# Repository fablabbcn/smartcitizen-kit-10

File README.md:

Smart Citizen Kit
=================

**NOTE:** [Click here](https://github.com/fablabbcn/smartcitizen-kit-20) for the newer version of SCK 2.0+

**Smart Citizen Kit BETA version for the Ambient Sensor Board.**

### Download

* Download the latest firmware release [here](https://github.com/fablabbcn/Smart-Citizen-Kit/releases/latest).

### Hardware

* Firmware for the [SmartCitizen Ambient Kit](http://smartcitizen.me/pages/sck) 1.0 and 1.1.

* More hardware info [here](https://github.com/fablabbcn/Smart-Citizen-Kit/tree/master/hardware).

### Quick start

* Visit the project main documentation [docs.smartcitizen.me](http://docs.smartcitizen.me)

### Loading Firmware

**The firmware is totally compatible with Arduino. You can upload the firmware using the [Arduino IDE](http://arduino.cc/en/main/software).**

* For SmartCitizen Kit version 1.0 select `Tools/Boards/Arduino Leonardo` on the Arduino IDE (ATmega 32U4 at 16Mhz) 

* For SmartCitizen Kit version 1.1 select `Tools/Boards/Lylipad Arduino USB` on the Arduino IDE (ATmega 32U4 at 8Mhz) 

### Versions

The current firmware version in use is `0.9.4`.

We currently support the SD card version on as a diferent firmware `SDCARD`, currently `0.8.7 SDCARD`.

You can see the release history [here](https://github.com/fablabbcn/Smart-Citizen-Kit/releases)

You can see the hardware versions [here](https://github.com/fablabbcn/Smart-Citizen-Kit/blob/master/hardware/README.md)

### Advance References

* Setup commands reference in [sck-commands.md](https://github.com/fablabbcn/Smart-Citizen-Kit/blob/master/sck-commands.md)

* Basic documentation for creating your own Sensor Boards [here](https://github.com/fablabbcn/Smart-Citizen-Kit/wiki/Making-a-Shield)

* [Slideshow](https://speakerdeck.com/pral2a/smart-citizen-hardware-and-software) with project technical details

### Support and issues

* Forum [forum.smartcitizen.me](http://forum.smartcitizen.me)

### Contributions

* We are working on improving the firmware documentation for developers but still we encourage you to Fork the project and do a Pull request with your contributions.

## License

All the software unless stated is released under [GNU GPL v3.0](https://github.com/fablabbcn/smartcitizen-kit/blob/master/LICENSE) and the hardware design files under [CERN OHL v1.2](https://github.com/fablabbcn/smartcitizen-kit/blob/master/hardware/LICENSE)

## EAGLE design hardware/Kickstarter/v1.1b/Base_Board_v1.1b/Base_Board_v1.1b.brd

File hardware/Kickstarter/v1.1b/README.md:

Smart-Citizen-Kit
=================

Eagles files of the Kickstarter campaign

[https://www.kickstarter.com/projects/acrobotic/the-smart-citizen-kit-crowdsourced-environmental-m
](https://www.kickstarter.com/projects/acrobotic/the-smart-citizen-kit-crowdsourced-environmental-m)

Smart Citizen Kit BETA version
- Base Board v1.1b
- Ambient Sensor Board v1.1b

The SCK is a piece of hardware comprised by two printed-circuit boards: an interchangeable daughterboard or shield, and an arduino-compatible data-processing board.

The sensor board carries sensors that measure air composition (CO and NO2), temperature, light intensity, sound levels, and humidity. Once it's set up, the ambient board is able to stream data measured by the sensors over Wi-Fi using the FCC-certified, wireless module on the data-processing board.

LICENSE: GPL v.0.3

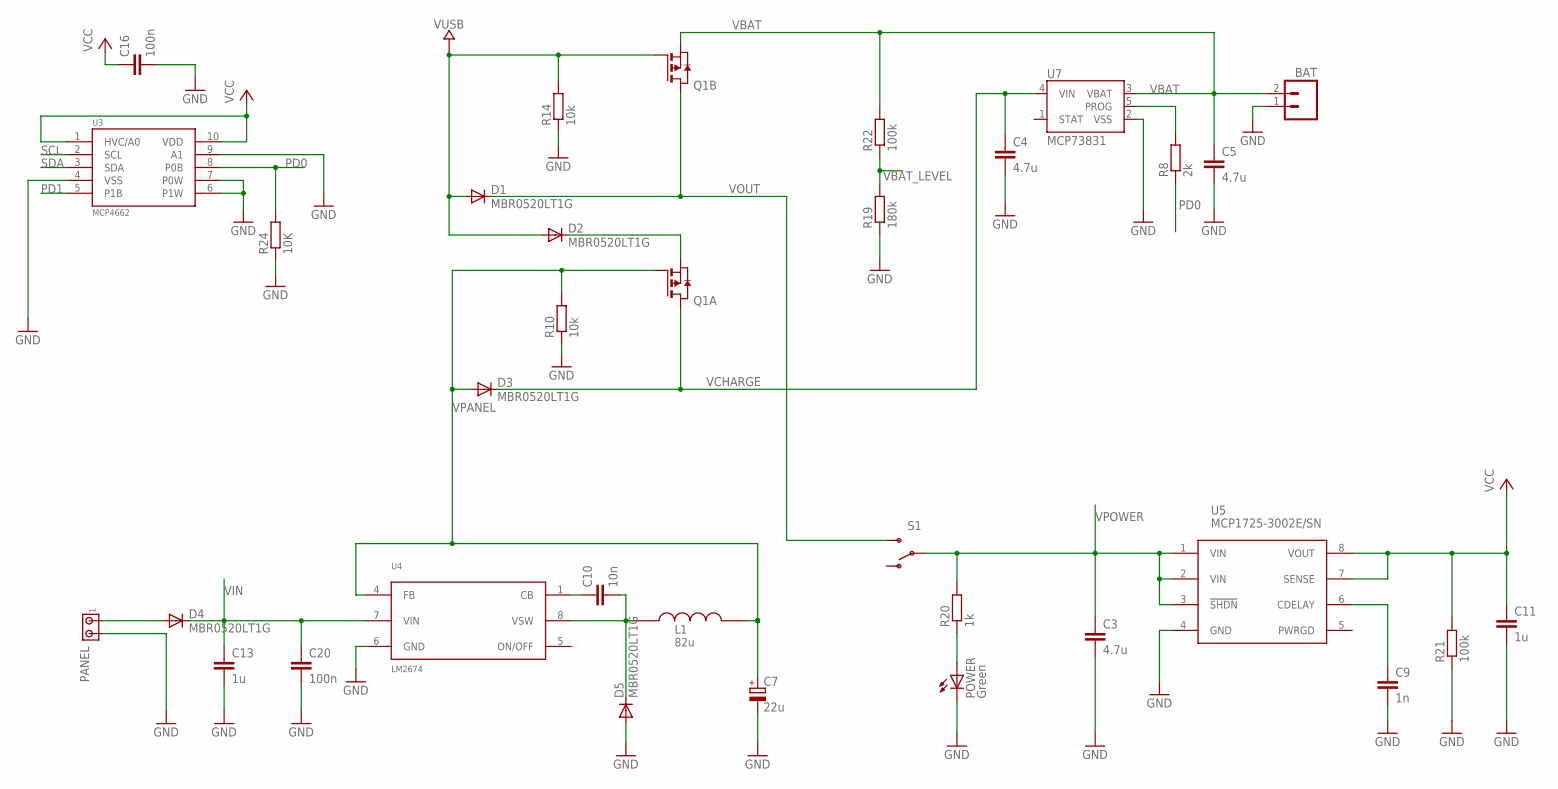
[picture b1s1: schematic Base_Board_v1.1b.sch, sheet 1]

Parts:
BAT: M02-JST-2MM-SMT; S2B-PH
C3, C4, C5: 4.7u; C0805
C7: 22u; SMC_A
C9: 1n; C0603K
C10: 10n; C0603K
C11, C13: 1u; C0805
C16, C20: 100n; C0603K
D1, D2, D3, D4, D5: MBR0520LT1G; SOD123
L1: 82u; SDR1006
PANEL: MTA02-100; 10X02MTA
POWER: Green; CHIP-LED0805
Q1: PMOS2SO8; SO8
R8: 2k; R0603
R10, R14: 10k; R0603
R19: 180k; R0603
R20: 1k; R0603
R21, R22: 100k; R0603
R24: 10K; R0603
S1: SWITCH-SPST-SMD-A
U3: MCP4662; MSOP10
U4: LM2674; SO8
U5: MCP1725-3002E/SN; SOIC8
U7: MCP73831; SOT23-5

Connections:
GND: BAT.1, C3.2, C4.2, C5.2, C7.-, C9.2, C11.2, C13.2, C16.2, C20.2, D5.A, PANEL.2, POWER.C, R10.1, R14.1, R19.1, R21.1, R24.1, U3.4 (VSS), U3.6 (P1W), U3.7 (P0W), U3.9 (A1), U4.6 (GND), U5.4 (GND), U7.2 (VSS); also elsewhere on the board
unnamed: D2.C, Q1.1 (S)
unnamed: D4.A, PANEL.1
unnamed: C9.1, U5.6 (CDELAY)
unnamed: R8.2, U7.5 (PROG)
unnamed: POWER.A, R20.1
unnamed: C10.1, U4.1 (CB)
unnamed: C10.2, D5.C, L1.1, U4.8 (VSW)
PD0: R8.1, R24.2, U3.8 (P0B)
PD1: U3.5 (P1B)
SCL: U3.2 (SCL); also elsewhere on the board
SDA: U3.3 (SDA); also elsewhere on the board
VBAT: BAT.2, C5.1, Q1.3 (S), R22.2, U7.3 (VBAT)
VBAT_LEVEL: R19.2, R22.1; also elsewhere on the board
VCC: C11.1, C16.1, R21.2, U3.1 (HVC/A0), U3.10 (VDD), U5.7 (SENSE), U5.8 (VOUT); also elsewhere on the board
VCHARGE: C4.1, D3.C, Q1.7 (D), Q1.8 (D), U7.4 (VIN)
VIN: C13.1, C20.1, D4.C, U4.7 (VIN); also elsewhere on the board
VOUT: D1.C, Q1.5 (D), Q1.6 (D), S1.3 (S)
VPANEL: C7.+, D3.A, L1.2, Q1.2 (G), R10.2, U4.4 (FB)
VPOWER: C3.1, R20.2, S1.2, U5.1 (VIN), U5.2 (VIN), U5.3 (!SHDN); also elsewhere on the board
VUSB: D1.A, D2.A, Q1.4 (G), R14.2; also elsewhere on the board

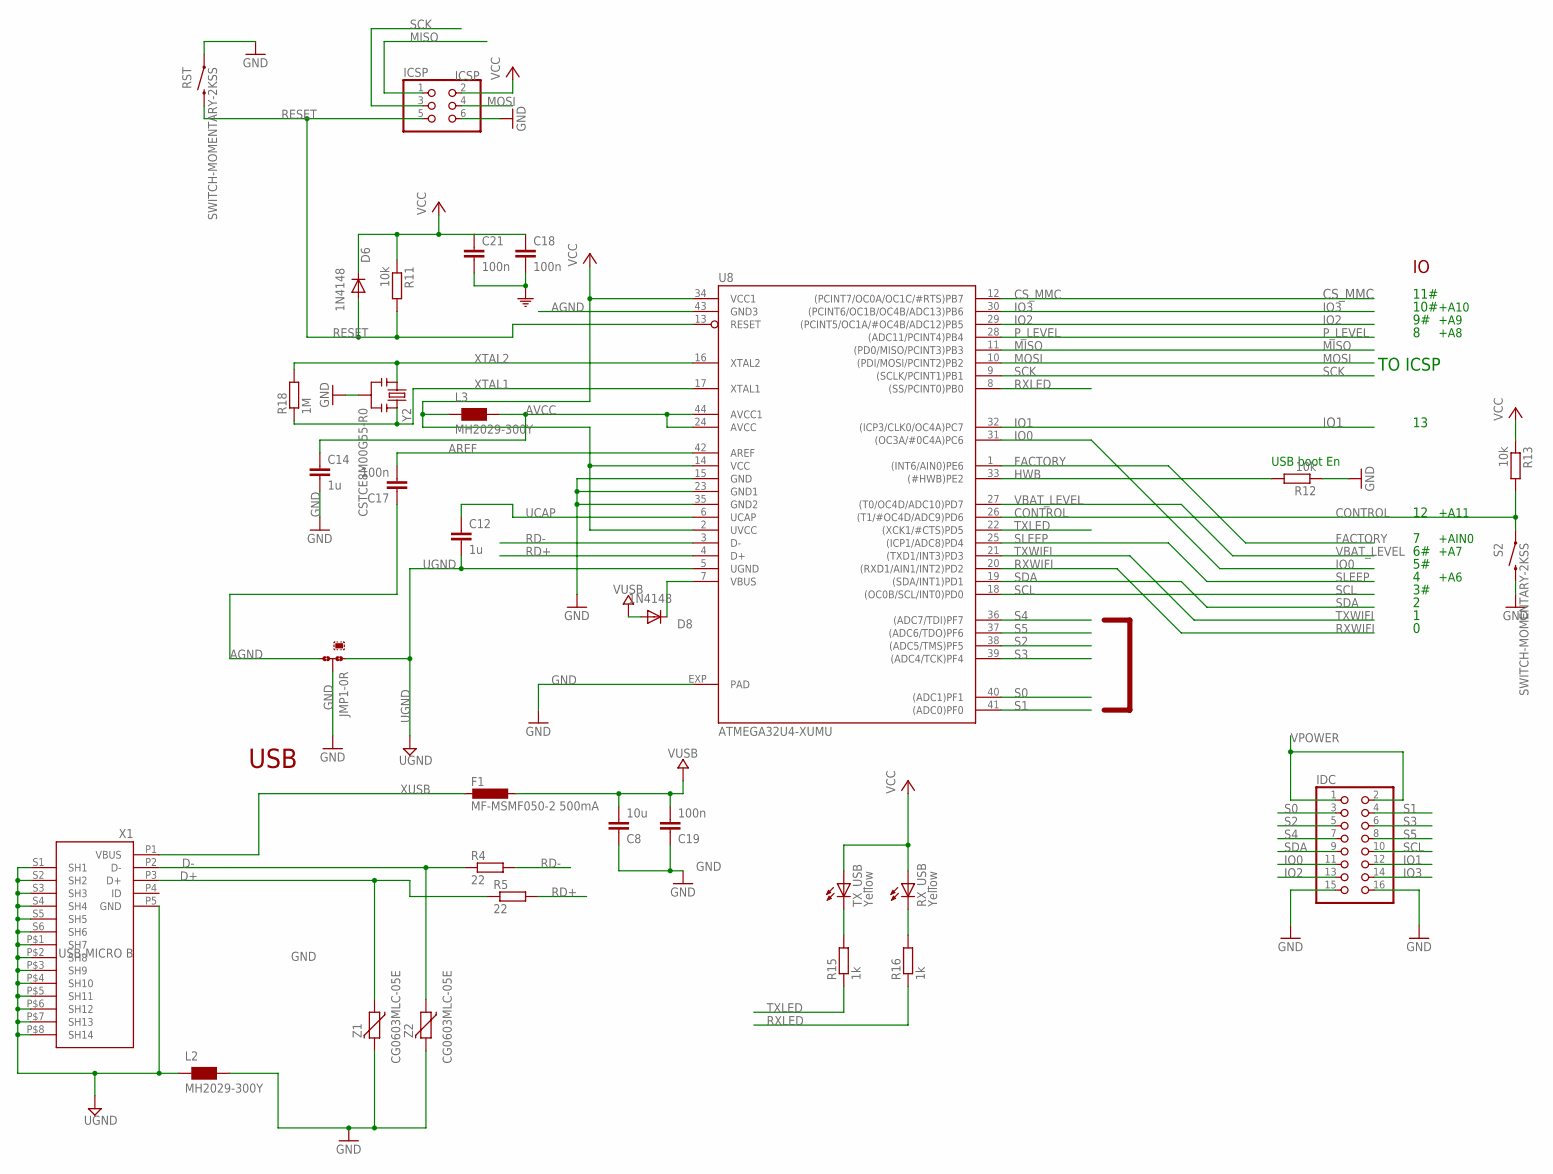
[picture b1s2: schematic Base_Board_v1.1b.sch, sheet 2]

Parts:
C8: 10u; C0805
C12, C14: 1u; C0805
C17, C18, C19, C21: 100n; C0603K
D6, D8: 1N4148; SOD323-W
F1: MF-MSMF050-2 500mA; L1812
ICSP: ICSP; 2X03
IDC: PINHD-2X8; 2X08
JMP1: 0R-JUMPC; C0R-JMP
L2, L3: MH2029-300Y; 0805
R4, R5: 22; R0603
R11, R12, R13: 10k; R0603
R15, R16: 1k; R0603
R18: 1M; R0603
RST: SWITCH-MOMENTARY-2KSS; KSS241G
RX_USB: Yellow; CHIP-LED0805
S2: SWITCH-MOMENTARY-2KSS; KSS241G
TX_USB: Yellow; CHIP-LED0805
U8: ATMEGA32U4-XUMU; QFN44ML7X7
X1: USB-MICRO B; CON2_USB_MICRO_B_AT
Y2: CSTCE8M00G55-R0
Z1, Z2: CG0603MLC-05E; CT/CN0603

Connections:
AGND: C17.1, JMP1.3, U8.43 (GND3)
AREF: C17.2, U8.42 (AREF)
AVCC: C14.1, L3.2, U8.24 (AVCC), U8.44 (AVCC1)
CONTROL: R13.2, S2.1, U8.26 ((T1/#OC4D/ADC9)PD6)
CS_MMC: U8.12 ((PCINT7/OC0A/OC1C/#RTS)PB7); also elsewhere on the board
D+: R5.1, X1.P3 (D+), Z1.1
D-: R4.1, X1.P2 (D-), Z2.1
FACTORY: U8.1 ((INT6/AIN0)PE6); also elsewhere on the board
GND: C8.1, C14.2, C18.2, C19.1, C21.2, ICSP.6, IDC.15, IDC.16, JMP1.2, L2.2, R12.1, RST.1, S2.2, U8.15 (GND), U8.23 (GND1), U8.35 (GND2), U8.EXP (PAD), Y2.2, Z1.2, Z2.2; also elsewhere on the board
GND1: L2.1, X1.P5 (GND), X1.P$1 (SH7), X1.P$2 (SH8), X1.P$3 (SH9), X1.P$4 (SH10), X1.P$5 (SH11), X1.P$6 (SH12), X1.P$7 (SH13), X1.P$8 (SH14), X1.S1 (SH1), X1.S2 (SH2), X1.S3 (SH3), X1.S4 (SH4), X1.S5 (SH5), X1.S6 (SH6)
HWB: R12.2, U8.33 ((#HWB)PE2)
IO0: IDC.11, U8.31 ((OC3A/#0C4A)PC6)
IO1: IDC.12, U8.32 ((ICP3/CLK0/OC4A)PC7)
IO2: IDC.13, U8.29 ((PCINT5/OC1A/#OC4B/ADC12)PB5)
IO3: IDC.14, U8.30 ((PCINT6/OC1B/OC4B/ADC13)PB6)
MISO: ICSP.1, U8.11 ((PD0/MISO/PCINT3)PB3); also elsewhere on the board
MOSI: ICSP.4, U8.10 ((PDI/MOSI/PCINT2)PB2); also elsewhere on the board
unnamed: R15.2, TX_USB.C
unnamed: R16.2, RX_USB.C
unnamed: D8.C, U8.7 (VBUS)
P_LEVEL: U8.28 ((ADC11/PCINT4)PB4); also elsewhere on the board
RD+: R5.2, U8.4 (D+)
RD-: R4.2, U8.3 (D-)
RESET: D6.A, ICSP.5, R11.2, RST.2, U8.13 (RESET); also elsewhere on the board
RXLED: R16.1, U8.8 ((SS/PCINT0)PB0)
RXWIFI: U8.20 ((RXD1/AIN1/INT2)PD2); also elsewhere on the board
S0: IDC.3, U8.40 ((ADC1)PF1)
S1: IDC.4, U8.41 ((ADC0)PF0)
S2: IDC.5, U8.38 ((ADC5/TMS)PF5)
S3: IDC.6, U8.39 ((ADC4/TCK)PF4)
S4: IDC.7, U8.36 ((ADC7/TDI)PF7)
S5: IDC.8, U8.37 ((ADC6/TDO)PF6)
SCK: ICSP.3, U8.9 ((SCLK/PCINT1)PB1); also elsewhere on the board
SCL: IDC.10, U8.18 ((OC0B/SCL/INT0)PD0); also elsewhere on the board
SDA: IDC.9, U8.19 ((SDA/INT1)PD1); also elsewhere on the board
SLEEP: U8.25 ((ICP1/ADC8)PD4); also elsewhere on the board
TXLED: R15.1, U8.22 ((XCK1/#CTS)PD5)
TXWIFI: U8.21 ((TXD1/INT3)PD3); also elsewhere on the board
UCAP: C12.1, U8.6 (UCAP)
UGND: C12.2, JMP1.1, U8.5 (UGND)
VBAT_LEVEL: U8.27 ((T0/OC4D/ADC10)PD7); also elsewhere on the board
VCC: C18.1, C21.1, D6.C, ICSP.2, L3.1, R11.1, R13.1, RX_USB.A, TX_USB.A, U8.2 (UVCC), U8.14 (VCC), U8.34 (VCC1); also elsewhere on the board
VPOWER: IDC.1, IDC.2; also elsewhere on the board
VUSB: C8.2, C19.2, D8.A, F1.1; also elsewhere on the board
XTAL1: R18.1, U8.17 (XTAL1), Y2.3
XTAL2: R18.2, U8.16 (XTAL2), Y2.1
XUSB: F1.2, X1.P1 (VBUS)

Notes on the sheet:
USB boot En
USB
TO ICSP
10#
11#
+A6
+A11
+A10
+A9
+A7
+A8
+AIN0

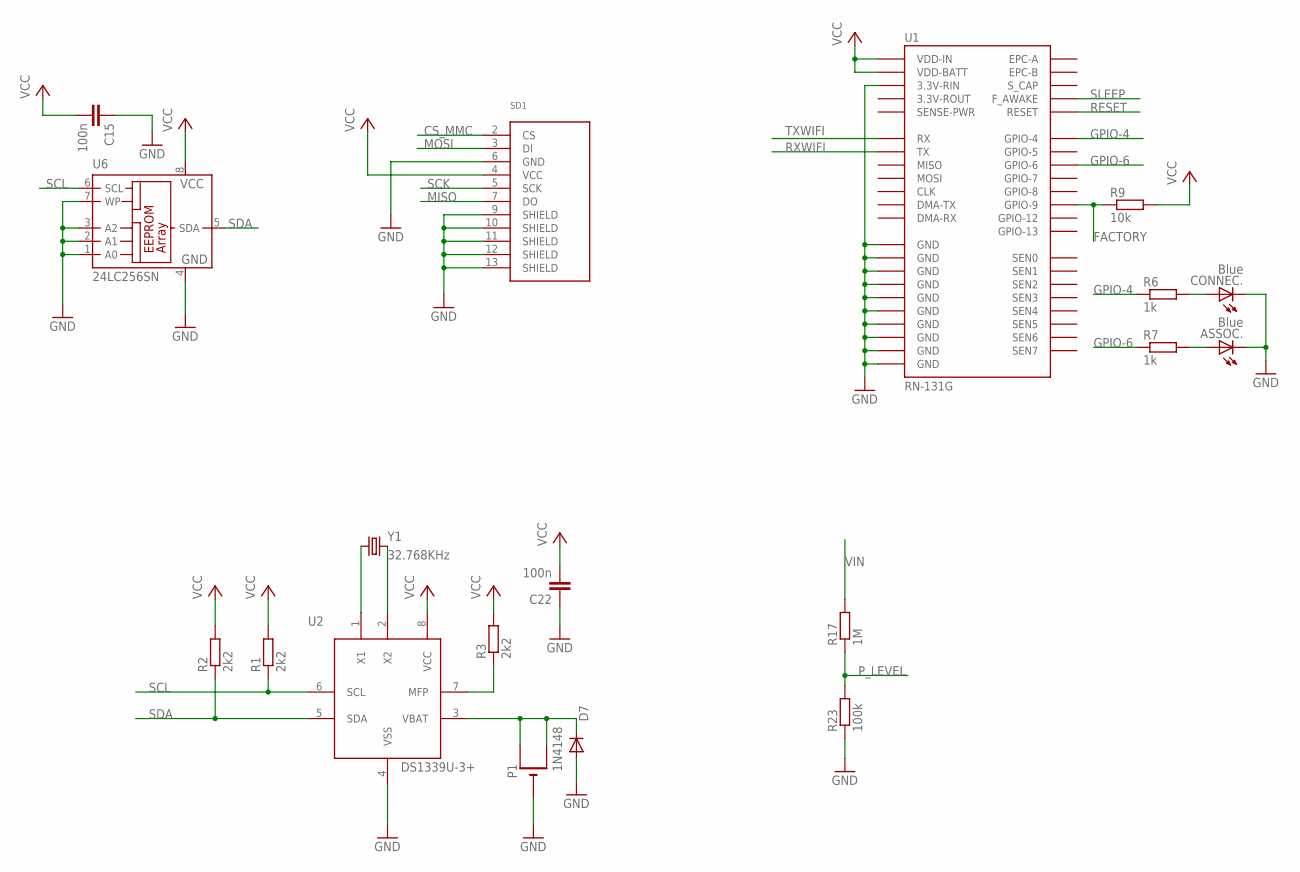
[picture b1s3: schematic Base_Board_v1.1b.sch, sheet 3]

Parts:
ASSOC.: Blue; CHIP-LED0805
C15, C22: 100n; C0603K
CONNEC.: Blue; CHIP-LED0805
D7: 1N4148; SOD323-W
P1: CR1220SMT; CR1220-SMD
R1, R2, R3: 2k2; R0603
R6, R7: 1k; R0603
R9: 10k; R0603
R17: 1M; R0603
R23: 100k; R0603
SD1: SD_CARD_SOCKETDM3CS; DM3CS
U1: RN-131G
U2: DS1339U-3+; MSOP-8
U6: 24LC256SN; SO-08
Y1: 32.768KHz; ABS10

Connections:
CS_MMC: SD1.2 (CS); also elsewhere on the board
FACTORY: R9.1, U1.P$24 (GPIO-9); also elsewhere on the board
GND: ASSOC..C, C15.1, C22.1, CONNEC..C, D7.A, P1.-, R23.1, SD1.6 (GND), SD1.9 (SHIELD), SD1.10 (SHIELD), SD1.11 (SHIELD), SD1.12 (SHIELD), SD1.13 (SHIELD), U1.P$18 (3.3V-RIN), U1.P$19 (GND), U1.P$36 (GND), U1.P$37 (GND), U1.P$38 (GND), U1.P$39 (GND), U1.P$40 (GND), U1.P$41 (GND), U1.P$42 (GND), U1.P$43 (GND), U1.P$44 (GND), U2.4 (VSS), U6.1 (A0), U6.2 (A1), U6.3 (A2), U6.4 (GND), U6.7 (WP); also elsewhere on the board
GPIO-4: R6.1, U1.P$29 (GPIO-4)
GPIO-6: R7.1, U1.P$27 (GPIO-6)
MISO: SD1.7 (DO); also elsewhere on the board
MOSI: SD1.3 (DI); also elsewhere on the board
unnamed: ASSOC..A, R7.2
unnamed: R3.1, U2.7 (MFP)
unnamed: CONNEC..A, R6.2
unnamed: U2.1 (X1), Y1.1
unnamed: U2.2 (X2), Y1.2
unnamed: D7.C, P1.+$1 (+), P1.+$2 (+1), U2.3 (VBAT)
P_LEVEL: R17.1, R23.2; also elsewhere on the board
RESET: U1.P$5 (RESET); also elsewhere on the board
RXWIFI: U1.P$13 (TX); also elsewhere on the board
SCK: SD1.5 (SCK); also elsewhere on the board
SCL: R1.1, U2.6 (SCL), U6.6 (SCL); also elsewhere on the board
SDA: R2.1, U2.5 (SDA), U6.5 (SDA); also elsewhere on the board
SLEEP: U1.P$9 (F_AWAKE); also elsewhere on the board
TXWIFI: U1.P$12 (RX); also elsewhere on the board
VCC: C15.2, C22.2, R1.2, R2.2, R3.2, R9.2, SD1.4 (VCC), U1.P$20 (VDD-BATT), U1.P$21 (VDD-IN), U2.8 (VCC), U6.8 (VCC); also elsewhere on the board
VIN: R17.2; also elsewhere on the board

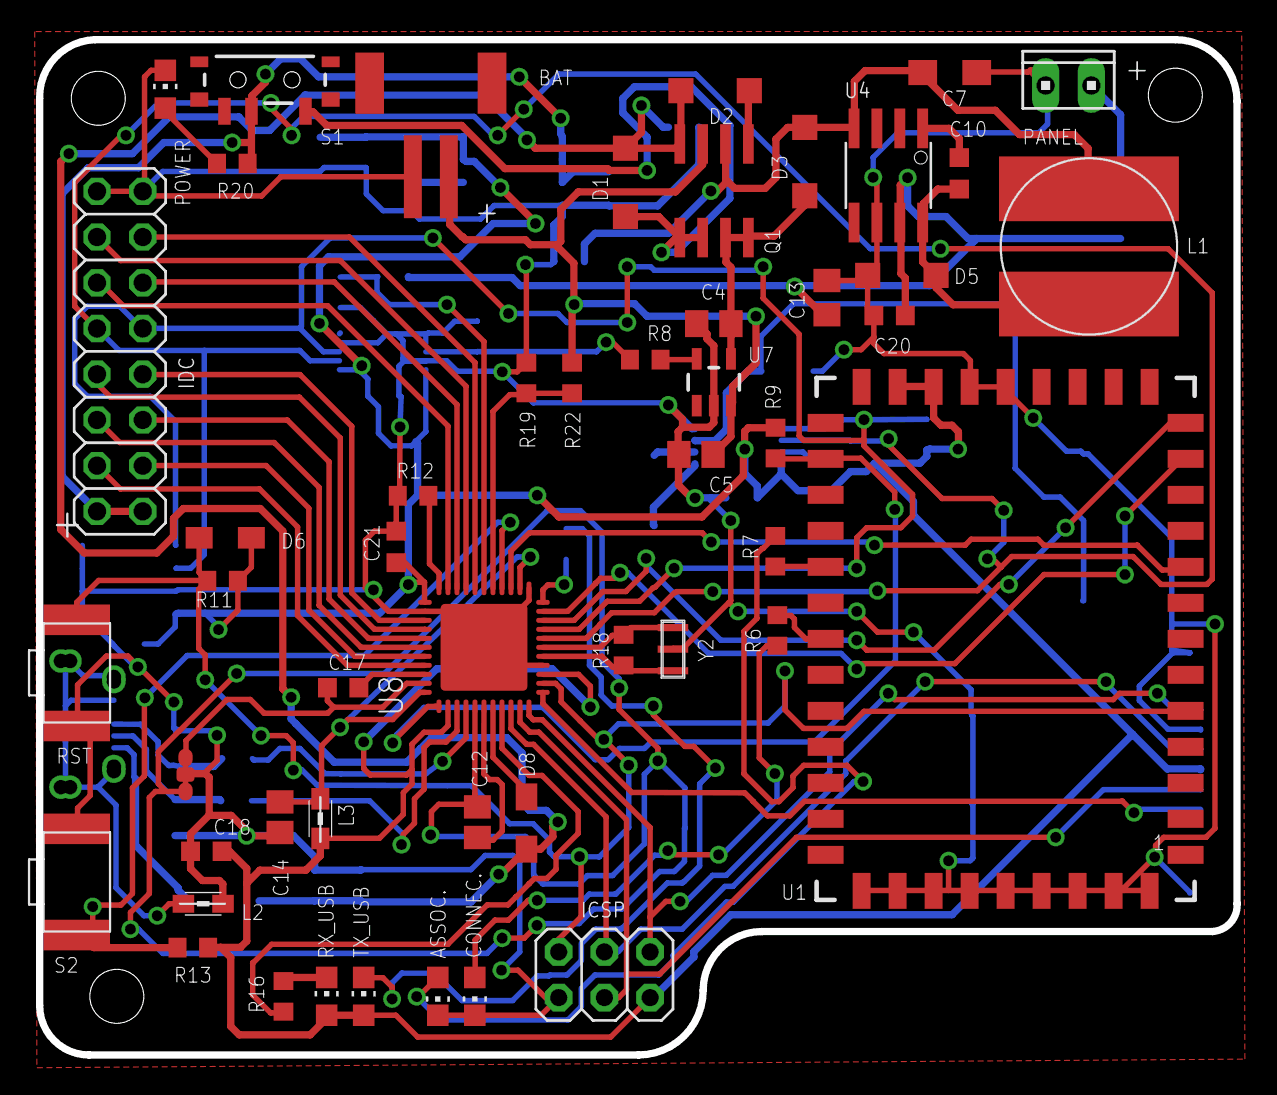
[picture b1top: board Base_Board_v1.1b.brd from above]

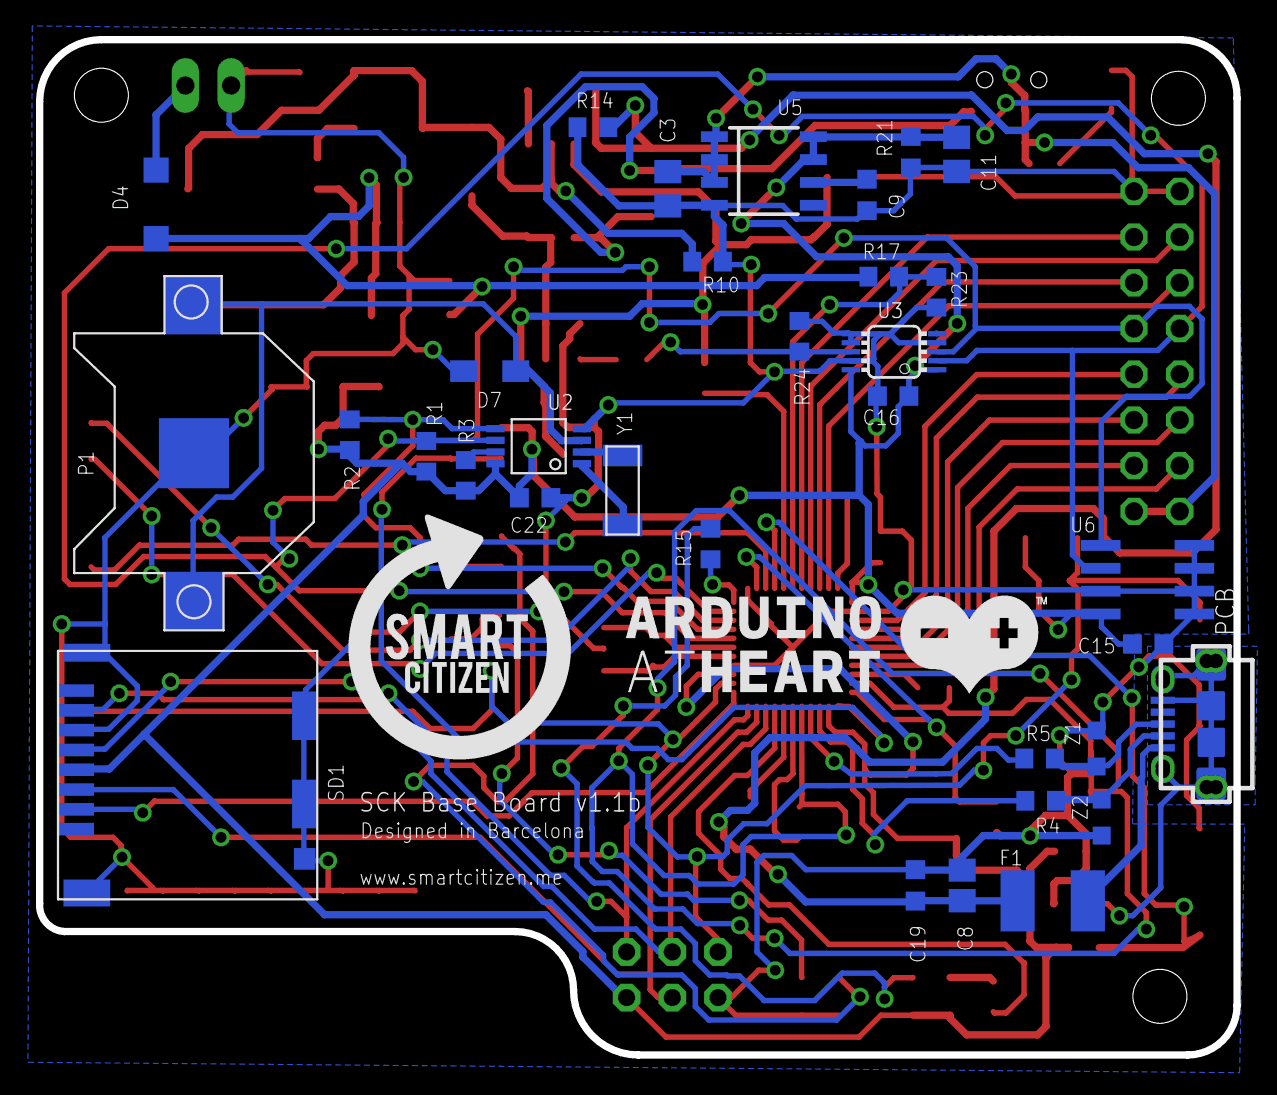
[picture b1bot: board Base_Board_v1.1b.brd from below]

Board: 2 copper layers, 66.5 x 56.4 mm, 84 parts (33 on the bottom side), 68 nets.

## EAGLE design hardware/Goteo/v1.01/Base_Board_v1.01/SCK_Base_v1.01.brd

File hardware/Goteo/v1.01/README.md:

Smart-Citizen-Kit
=================

Eagles files of Goteo.org campaign, 2n release

[http://www.goteo.org/project/smart-citizen-sensores-ciudadanos?lang=en
](http://www.goteo.org/project/smart-citizen-sensores-ciudadanos?lang=en)

Smart Citizen Kit BETA version
- Base Board v1.01
- Ambient Sensor Board v1.01

The SCK is a piece of hardware comprised by two printed-circuit boards: an interchangeable daughterboard or shield, and an arduino-compatible data-processing board.

The sensor board carries sensors that measure air composition (CO and NO2), temperature, light intensity, sound levels, and humidity. Once it's set up, the ambient board is able to stream data measured by the sensors over Wi-Fi using the FCC-certified, wireless module on the data-processing board.

LICENSE: GPL v.0.3

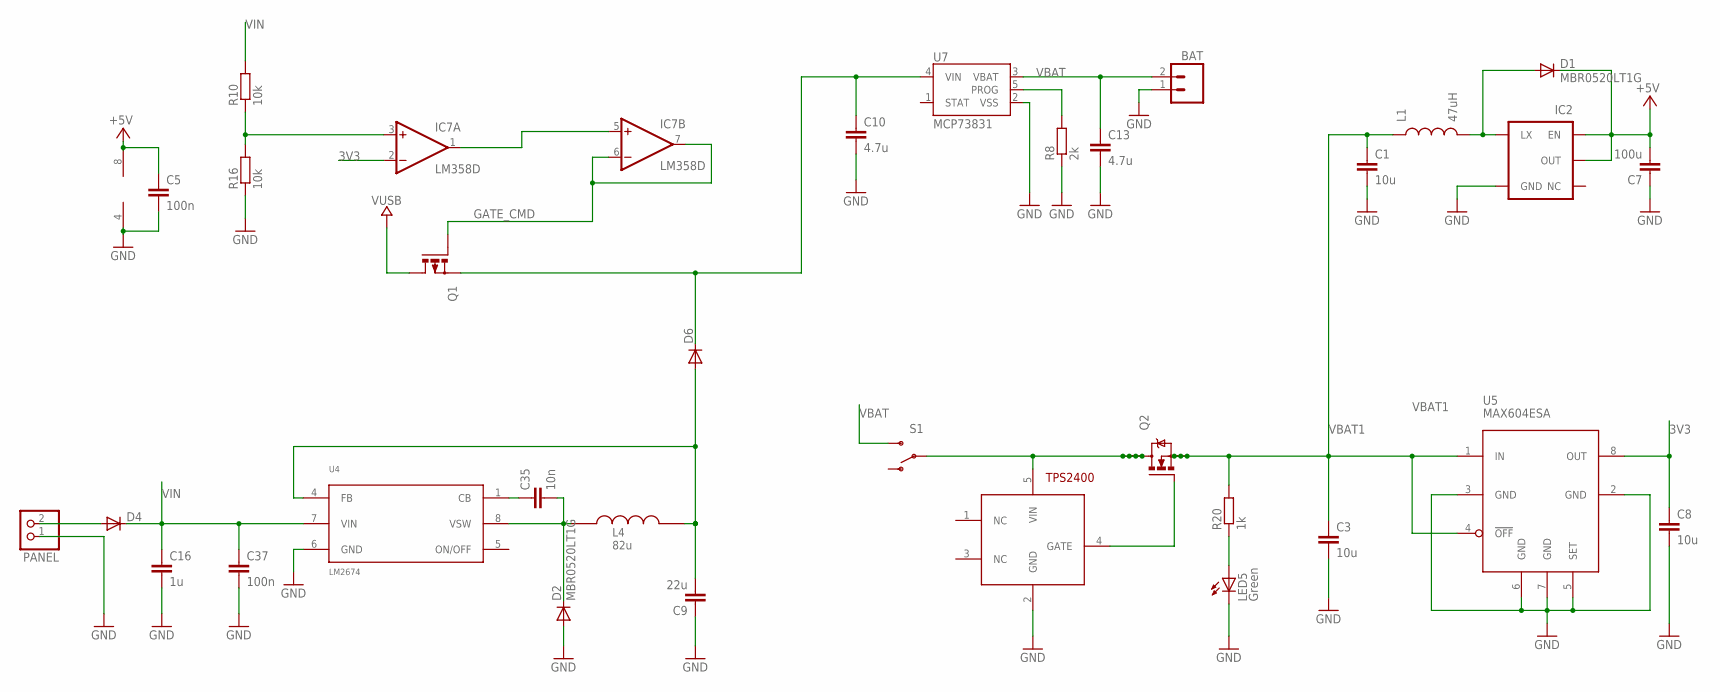
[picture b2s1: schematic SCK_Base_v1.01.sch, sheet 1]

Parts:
BAT: M02-JST-2MM-SMT; S2B-PH
C1, C3, C8: 10u; C0805
C5, C37: 100n; C0805
C7: 100u; C1206
C9: 22u; C1206
C10, C13: 4.7u; C0805
C16: 1u; C0805
C35: 10n; C0805
D1, D2: MBR0520LT1G; SOD123
D4, D6: DIODESMA-ALT; SMA-DIODE_ALT
IC2: V_REG_NCP1400SOT23-5; SOT23-5
IC7: LM358D; SO08
L1: 47uH; CR54
L4: 82u; SDR1006
LED5: Green; CHIP-LED0805
PANEL: PINHD-1X2; 1X02
Q1: P-MOSFET-SO8; SO-08
Q2: N-MOSFET-SO8S; SO-08
R8: 2k; R0805
R10, R16: 10k; R0805
R20: 1k; R0805
S1: SWITCH-SPST-SMD-A
U3: TPS2400; SOT23-5L
U4: LM2674; SO8
U5: MAX604ESA; SO-08
U7: MCP73831; SOT23-5

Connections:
3V3: C8.1, IC7.2 (-IN), U5.8 (OUT); also elsewhere on the board
+5V: C5.1, C7.2, D1.C, IC2.1 (EN), IC2.2 (OUT), IC7.8 (V+); also elsewhere on the board
GATE_CMD: IC7.6 (-IN), IC7.7 (OUT), Q1.4 (G)
GND: BAT.1, C1.2, C3.2, C5.2, C7.1, C8.2, C9.1, C10.2, C13.2, C16.2, C37.2, D2.A, IC2.4 (GND), IC7.4 (V-), LED5.C, PANEL.1, R8.1, R16.1, U3.2 (GND), U4.6 (GND), U5.2 (GND), U5.3 (GND), U5.5 (SET), U5.6 (GND), U5.7 (GND), U7.2 (VSS); also elsewhere on the board
unnamed: D4.A, PANEL.2
unnamed: IC7.3 (+IN), R10.1, R16.2
unnamed: IC7.1 (OUT), IC7.5 (+IN)
unnamed: C9.2, D6.A, L4.2, U4.4 (FB)
unnamed: R8.2, U7.5 (PROG)
unnamed: C10.1, D6.C, Q1.1 (S), Q1.2 (S), Q1.3 (S), U7.4 (VIN)
unnamed: LED5.A, R20.1
unnamed: Q2.4 (G), U3.4 (GATE)
unnamed: D1.A, IC2.5 (LX), L1.P$2 (2)
unnamed: C35.1, U4.1 (CB)
unnamed: C35.2, D2.C, L4.1, U4.8 (VSW)
VBAT: BAT.2, C13.1, S1.3 (S), U7.3 (VBAT)
VBAT1: C1.1, C3.1, L1.P$1 (1), Q2.1 (S), Q2.2 (S), Q2.3 (S), R20.2, U5.1 (IN), U5.4 (!OFF); also elsewhere on the board
VIN: C16.1, C37.1, D4.C, R10.2, U4.7 (VIN); also elsewhere on the board
VTPS: Q2.5 (D), Q2.6 (D), Q2.7 (D), Q2.8 (D), S1.2, U3.5 (VIN)
VUSB: Q1.5 (D), Q1.6 (D), Q1.7 (D), Q1.8 (D); also elsewhere on the board

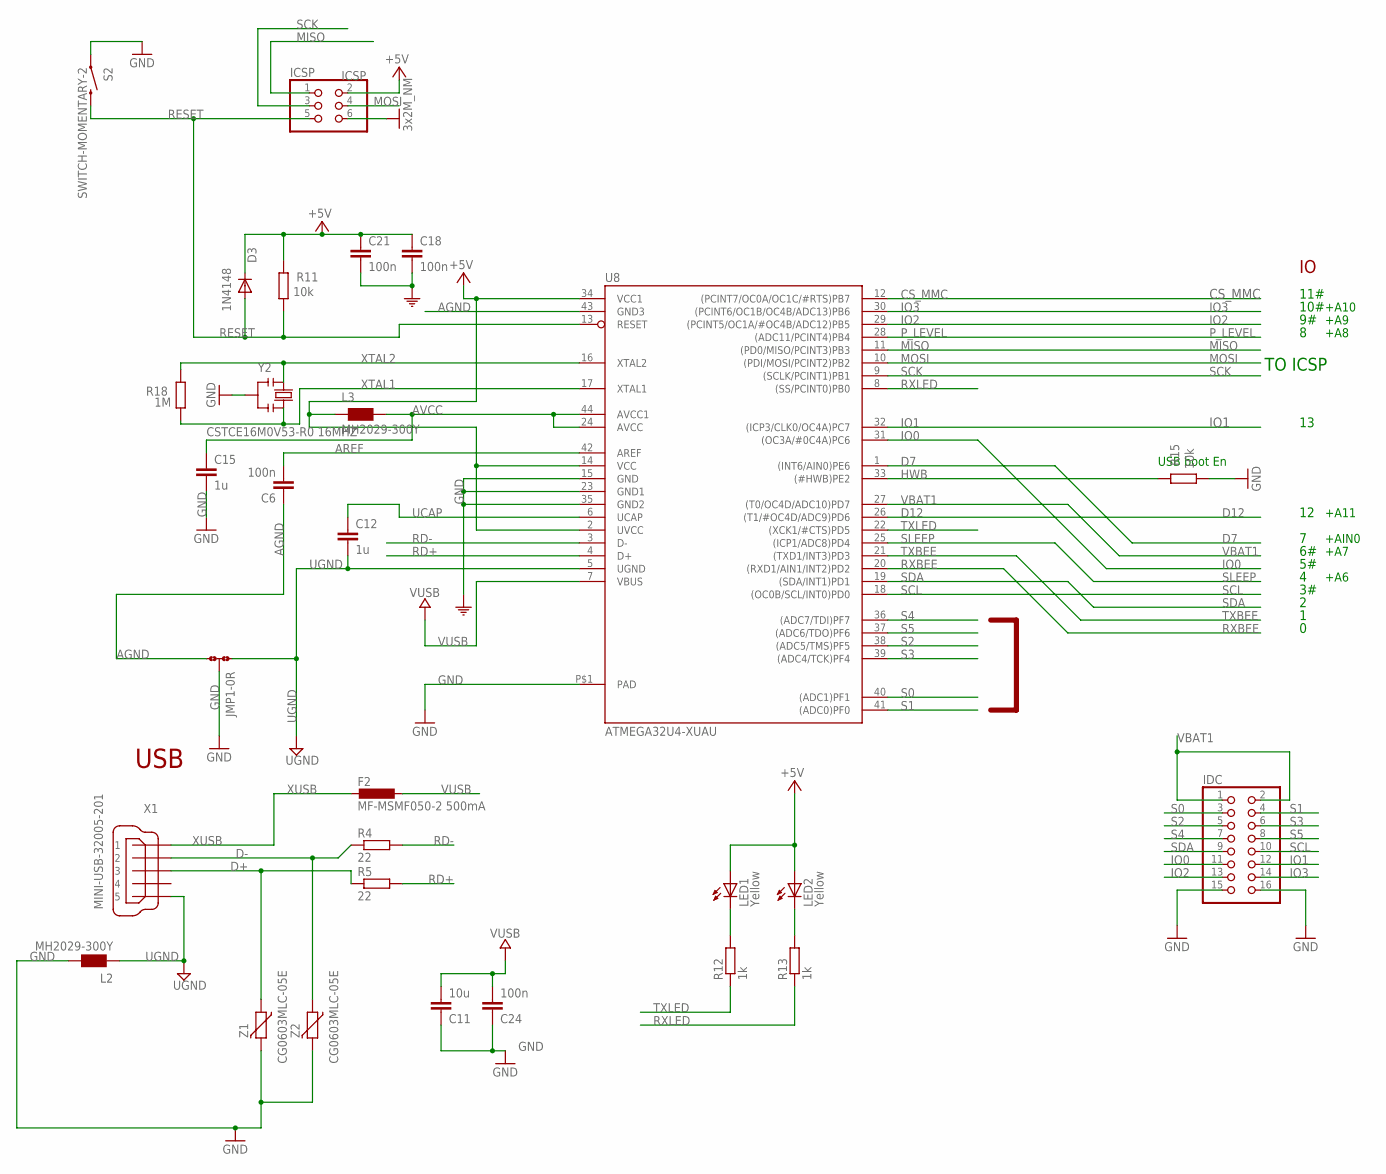
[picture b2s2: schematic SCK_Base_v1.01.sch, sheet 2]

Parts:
C6, C18, C21, C24: 100n; C0805
C11: 10u; C0805
C12, C15: 1u; C0805
D3: 1N4148; SOD123
F2: MF-MSMF050-2 500mA; L1812
ICSP: ICSP; 2X03
IDC: PINHD-2X8; 2X08
JMP1: 0R-JUMPC; C0R-JMP
L2, L3: MH2029-300Y; 0805
LED1, LED2: Yellow; CHIP-LED0805
R4, R5: 22; R0805
R11, R15: 10k; R0805
R12, R13: 1k; R0805
R18: 1M; R0805
S2: SWITCH-MOMENTARY-2; TACTILE_SWITCH_TALL
U8: ATMEGA32U4-XUAU; TQFP44-PAD
X1: MINI-USB-32005-201; 32005-201
Y2: CSTCE16M0V53-R0 16MHZ; RESONATOR
Z1, Z2: CG0603MLC-05E; CT/CN0603

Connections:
+5V: C18.1, C21.1, D3.C, ICSP.2, L3.1, LED1.A, LED2.A, R11.2, U8.2 (UVCC), U8.14 (VCC), U8.34 (VCC1); also elsewhere on the board
AGND: C6.1, JMP1.3, U8.43 (GND3)
AREF: C6.2, U8.42 (AREF)
AVCC: C15.1, L3.2, U8.24 (AVCC), U8.44 (AVCC1)
CS_MMC: U8.12 ((PCINT7/OC0A/OC1C/#RTS)PB7); also elsewhere on the board
D7: U8.1 ((INT6/AIN0)PE6)
D12: U8.26 ((T1/#OC4D/ADC9)PD6)
D+: R5.1, X1.3, Z1.1
D-: R4.1, X1.2, Z2.1
GND: C11.1, C15.2, C18.2, C21.2, C24.1, ICSP.6, IDC.15, IDC.16, JMP1.2, L2.2, R15.1, S2.A2 (1), U8.15 (GND), U8.23 (GND1), U8.35 (GND2), U8.P$1 (PAD), Y2.2, Z1.2, Z2.2; also elsewhere on the board
HWB: R15.2, U8.33 ((#HWB)PE2)
IO0: IDC.11, U8.31 ((OC3A/#0C4A)PC6)
IO1: IDC.12, U8.32 ((ICP3/CLK0/OC4A)PC7)
IO2: IDC.13, U8.29 ((PCINT5/OC1A/#OC4B/ADC12)PB5)
IO3: IDC.14, U8.30 ((PCINT6/OC1B/OC4B/ADC13)PB6)
MISO: ICSP.1, U8.11 ((PD0/MISO/PCINT3)PB3); also elsewhere on the board
MOSI: ICSP.4, U8.10 ((PDI/MOSI/PCINT2)PB2); also elsewhere on the board
unnamed: LED1.C, R12.2
unnamed: LED2.C, R13.2
P_LEVEL: U8.28 ((ADC11/PCINT4)PB4); also elsewhere on the board
RD+: R5.2, U8.4 (D+)
RD-: R4.2, U8.3 (D-)
RESET: D3.A, ICSP.5, R11.1, S2.B2 (2), U8.13 (RESET); also elsewhere on the board
RXBEE: U8.20 ((RXD1/AIN1/INT2)PD2); also elsewhere on the board
RXLED: R13.1, U8.8 ((SS/PCINT0)PB0)
S0: IDC.3, U8.40 ((ADC1)PF1)
S1: IDC.4, U8.41 ((ADC0)PF0)
S2: IDC.5, U8.38 ((ADC5/TMS)PF5)
S3: IDC.6, U8.39 ((ADC4/TCK)PF4)
S4: IDC.7, U8.36 ((ADC7/TDI)PF7)
S5: IDC.8, U8.37 ((ADC6/TDO)PF6)
SCK: ICSP.3, U8.9 ((SCLK/PCINT1)PB1); also elsewhere on the board
SCL: IDC.10, U8.18 ((OC0B/SCL/INT0)PD0); also elsewhere on the board
SDA: IDC.9, U8.19 ((SDA/INT1)PD1); also elsewhere on the board
SLEEP: U8.25 ((ICP1/ADC8)PD4); also elsewhere on the board
TXBEE: U8.21 ((TXD1/INT3)PD3); also elsewhere on the board
TXLED: R12.1, U8.22 ((XCK1/#CTS)PD5)
UCAP: C12.1, U8.6 (UCAP)
UGND: C12.2, JMP1.1, L2.1, U8.5 (UGND), X1.5
VBAT1: IDC.1, IDC.2, U8.27 ((T0/OC4D/ADC10)PD7); also elsewhere on the board
VUSB: C11.2, C24.2, F2.1, U8.7 (VBUS); also elsewhere on the board
XTAL1: R18.1, U8.17 (XTAL1), Y2.3
XTAL2: R18.2, U8.16 (XTAL2), Y2.1
XUSB: F2.2, X1.1

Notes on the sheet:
USB boot En
USB
TO ICSP
10#
11#
+A6
+A11
+A10
+A9
+A7
+A8
+AIN0

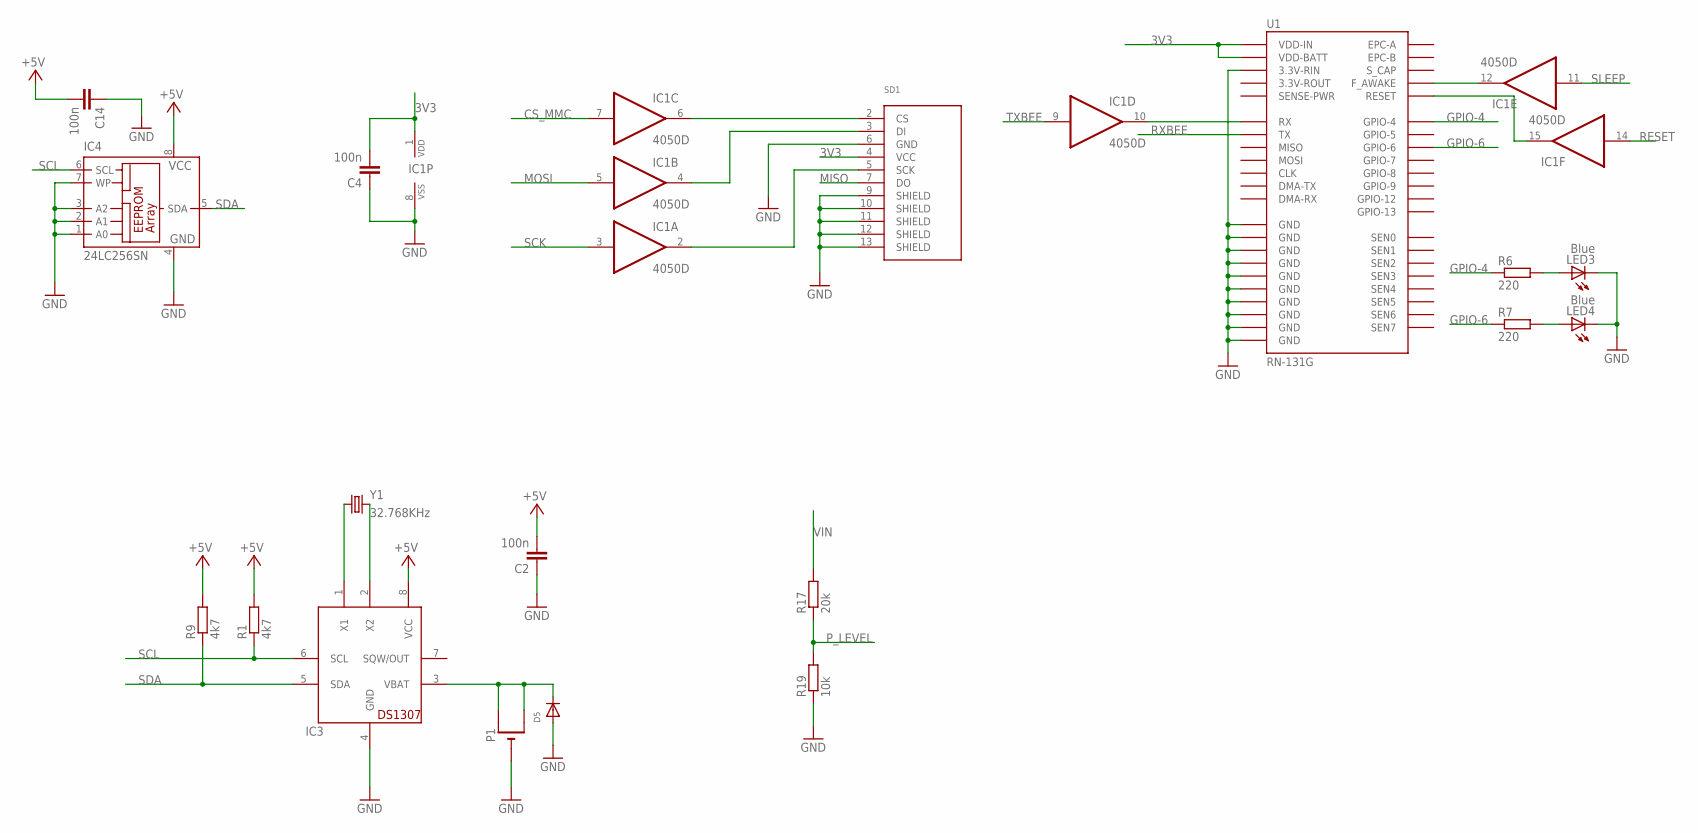
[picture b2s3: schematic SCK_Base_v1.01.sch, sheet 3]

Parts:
C2, C4, C14: 100n; C0805
D5: DIODESOD-323F; SOD-323F
IC1: 4050D; SO16
IC3: DS1307SOIC; SO08-SKINNYPADS
IC4: 24LC256SN; SO-08
LED3, LED4: Blue; CHIP-LED0805
P1: CR1220SMT; CR1220-SMD
R1, R9: 4k7; R0805
R6, R7: 220; R0805
R17: 20k; R0805
R19: 10k; R0805
SD1: SD_CARD_SOCKETDM3CS; DM3CS
U1: RN-131G
Y1: 32.768KHz; ABS10

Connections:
3V3: C4.2, IC1.1 (VDD), SD1.4 (VCC), U1.P$20 (VDD-BATT), U1.P$21 (VDD-IN); also elsewhere on the board
+5V: C2.2, C14.2, IC3.8 (VCC), IC4.8 (VCC), R1.2, R9.2; also elsewhere on the board
CS_MMC: IC1.7 (I); also elsewhere on the board
GND: C2.1, C4.1, C14.1, D5.A, IC1.8 (VSS), IC3.4 (GND), IC4.1 (A0), IC4.2 (A1), IC4.3 (A2), IC4.4 (GND), IC4.7 (WP), LED3.C, LED4.C, P1.-, R19.1, SD1.6 (GND), SD1.9 (SHIELD), SD1.10 (SHIELD), SD1.11 (SHIELD), SD1.12 (SHIELD), SD1.13 (SHIELD), U1.P$18 (3.3V-RIN), U1.P$19 (GND), U1.P$36 (GND), U1.P$37 (GND), U1.P$38 (GND), U1.P$39 (GND), U1.P$40 (GND), U1.P$41 (GND), U1.P$42 (GND), U1.P$43 (GND), U1.P$44 (GND); also elsewhere on the board
GPIO-4: R6.1, U1.P$29 (GPIO-4)
GPIO-6: R7.1, U1.P$27 (GPIO-6)
MISO: SD1.7 (DO); also elsewhere on the board
MOSI: IC1.5 (I); also elsewhere on the board
unnamed: IC1.10 (O), U1.P$12 (RX)
unnamed: LED4.A, R7.2
unnamed: LED3.A, R6.2
unnamed: IC1.6 (O), SD1.2 (CS)
unnamed: IC1.2 (O), SD1.5 (SCK)
unnamed: IC1.4 (O), SD1.3 (DI)
unnamed: IC1.12 (O), U1.P$9 (F_AWAKE)
unnamed: IC1.15 (O), U1.P$5 (RESET)
unnamed: IC3.1 (X1), Y1.1
unnamed: IC3.2 (X2), Y1.2
unnamed: D5.C, IC3.3 (VBAT), P1.+$1 (+), P1.+$2 (+1)
P_LEVEL: R17.1, R19.2; also elsewhere on the board
RESET: IC1.14 (I); also elsewhere on the board
RXBEE: U1.P$13 (TX); also elsewhere on the board
SCK: IC1.3 (I); also elsewhere on the board
SCL: IC3.6 (SCL), IC4.6 (SCL), R1.1; also elsewhere on the board
SDA: IC3.5 (SDA), IC4.5 (SDA), R9.1; also elsewhere on the board
SLEEP: IC1.11 (I); also elsewhere on the board
TXBEE: IC1.9 (I); also elsewhere on the board
VIN: R17.2; also elsewhere on the board

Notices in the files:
parts and their libraries:
SparkFun-PowerIC: Licensing: CC v3.0 Share-Alike You are welcome to use this library for commercial purposes.
